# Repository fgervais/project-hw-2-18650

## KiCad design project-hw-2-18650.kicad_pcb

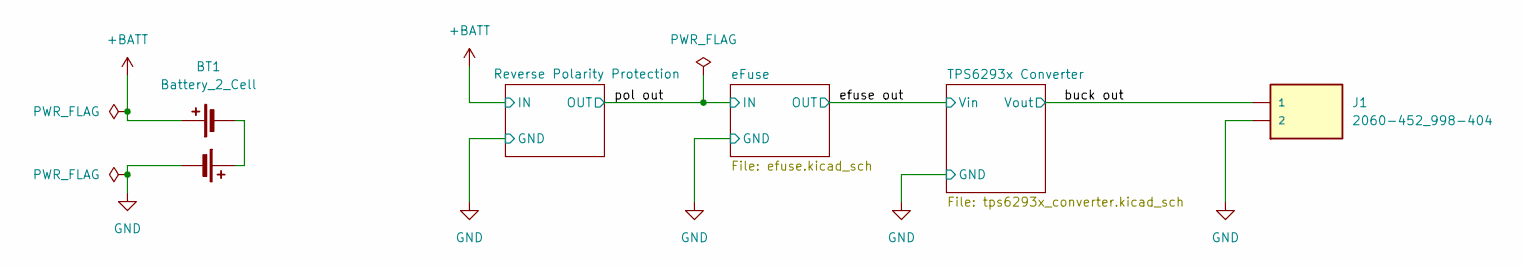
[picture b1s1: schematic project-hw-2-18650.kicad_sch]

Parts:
BT1: Battery_2_Cell; Keystone_1049P
J1: 2060-452_998-404; WAGO_2060-452_998-404; PARTREV N/A

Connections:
+BATT: BT1.1 (+); also elsewhere on the board
/buck out: J1.1_1 (1), J1.1_2 (1); also elsewhere on the board
GND: BT1.3 (-), J1.2_1 (2), J1.2_2 (2); also elsewhere on the board
unnamed: BT1.2 (-), BT1.4 (+)

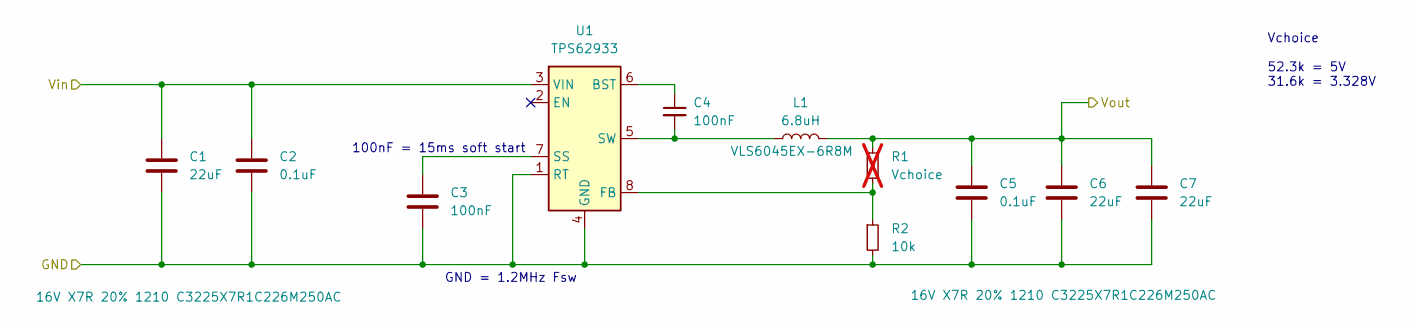
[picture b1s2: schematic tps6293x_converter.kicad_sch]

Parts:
C1, C6, C7: 22uF; C_1210_3225Metric
C2, C5: 0.1uF; C_0603_1608Metric
C3, C4: 100nF; C_0603_1608Metric
L1: 6.8uH; L_TDK_VLS6045EX_VLS6045AF
R1: Vchoice; 0603_1608Metric_DNI_NoPaste; not fitted
R2: 10k; R_0603_1608Metric
U1: TPS62933; SOT-583-8

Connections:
/buck out: C5.1, C6.1, C7.1, L1.2, R1.1; also elsewhere on the board
/efuse out: C1.1, C2.1, U1.3 (VIN); also elsewhere on the board
GND: C1.2, C2.2, C3.2, C5.2, C6.2, C7.2, R2.2, U1.1 (RT), U1.4 (GND); also elsewhere on the board
unnamed: C4.1, U1.6 (BST)
unnamed: R1.2, R2.1, U1.8 (FB)
unnamed: C3.1, U1.7 (SS)
unnamed: C4.2, L1.1, U1.5 (SW)

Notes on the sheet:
100nF = 15ms soft start
Vchoice 52.3k = 5V 31.6k = 3.328V
GND = 1.2MHz Fsw

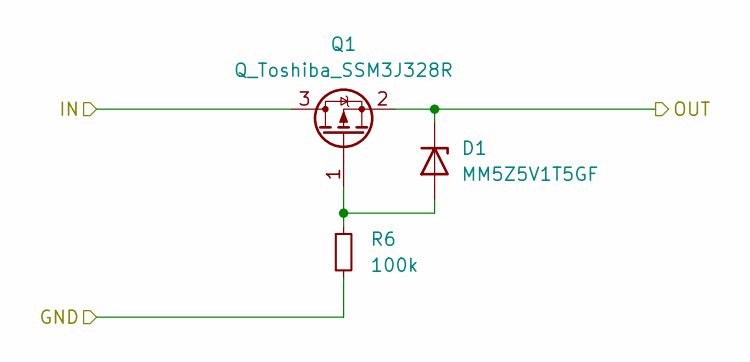
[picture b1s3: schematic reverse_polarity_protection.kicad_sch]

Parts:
D1: MM5Z5V1T5GF; D_SOD-523
Q1: Q_Toshiba_SSM3J328R; SOT-23F
R6: 100k; R_0603_1608Metric

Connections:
+BATT: Q1.3 (D); also elsewhere on the board
/pol out: D1.1 (K), Q1.2 (S); also elsewhere on the board
GND: R6.2; also elsewhere on the board
unnamed: D1.2 (A), Q1.1 (G), R6.1

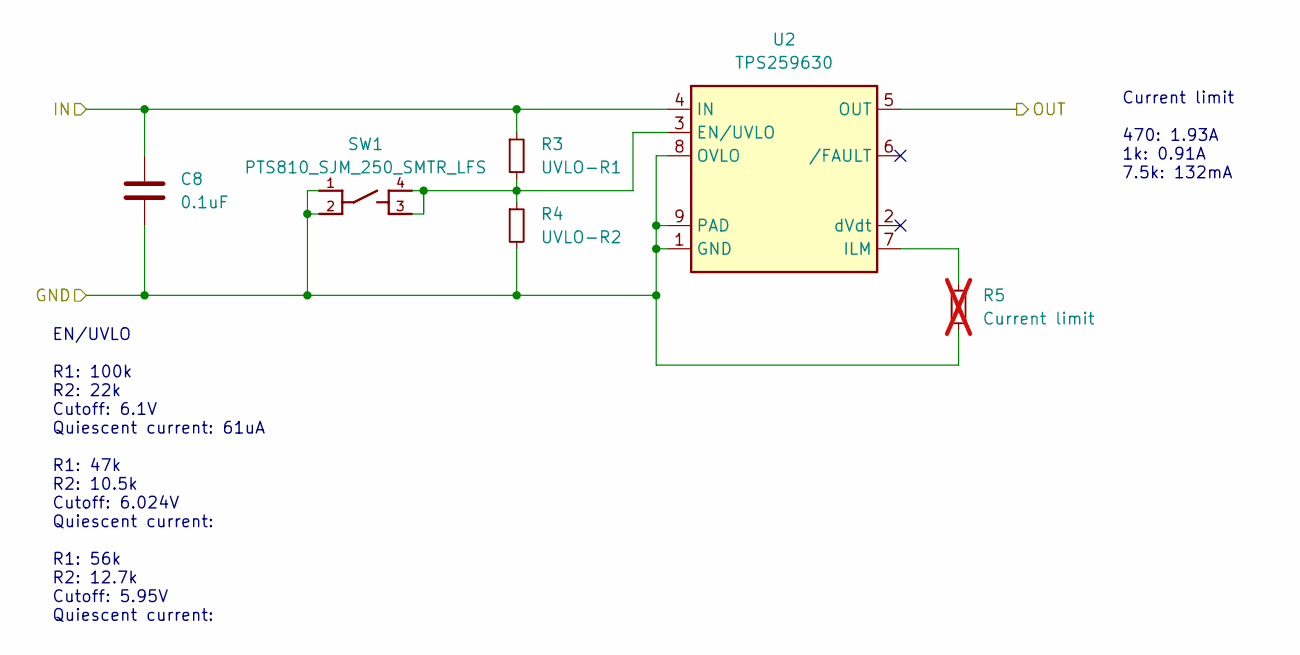
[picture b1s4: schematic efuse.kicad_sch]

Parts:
C8: 0.1uF; C_0603_1608Metric
R3: UVLO-R1; R_0603_1608Metric
R4: UVLO-R2; R_0603_1608Metric
R5: Current limit; 0603_1608Metric_DNI_NoPaste; not fitted
SW1: PTS810_SJM_250_SMTR_LFS; SW_PTS810_SJM_250_SMTR_LFS; DigiKey_Part_Number CKN10502TR-ND
U2: TPS259630; TI_SO-PowerPAD-8

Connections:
/efuse out: U2.5 (OUT); also elsewhere on the board
/pol out: C8.1, R3.1, U2.4 (IN); also elsewhere on the board
GND: C8.2, R4.2, R5.2, SW1.1, SW1.2, U2.1 (GND), U2.8 (OVLO), U2.9 (PAD); also elsewhere on the board
unnamed: R3.2, R4.1, SW1.3, SW1.4, U2.3 (EN/UVLO)
unnamed: R5.1, U2.7 (ILM)

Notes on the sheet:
Current limit 470: 1.93A 1k: 0.91A 7.5k: 132mA
EN/UVLO R1: 100k R2: 22k Cutoff: 6.1V Quiescent current: 61uA R1: 47k R2: 10.5k Cutoff: 6.024V Quiescent current: R1: 56k R2: 12.7k Cutoff: 5.95V Quiescent current:

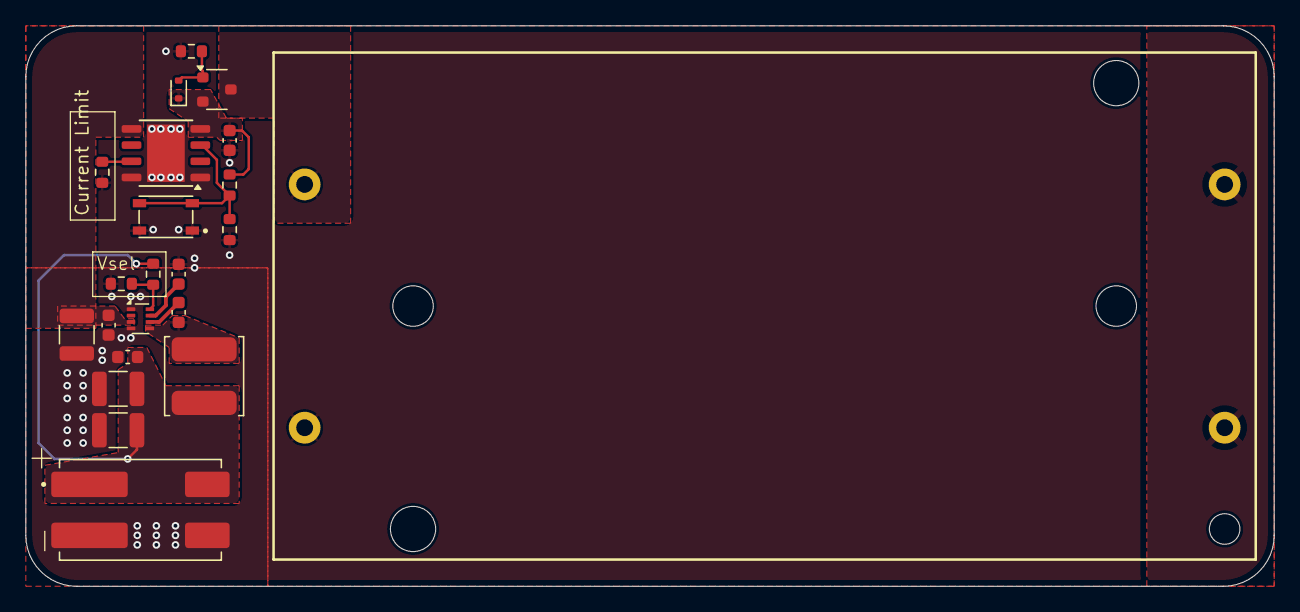
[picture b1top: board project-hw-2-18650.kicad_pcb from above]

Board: 2 copper layers, 98.0 x 44.0 mm, 22 parts (0 on the bottom side), 13 nets.

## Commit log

2025-09-26 Create blank project
2025-09-27 sch: first draft
2025-09-27 sch: assign correct footprint
2025-09-27 pcb: first draft
2025-09-27 pcb: change DNI footprint
2025-09-27 pcb: add ground backplane
2025-09-28 pcb: routing v2
2025-09-28 sch: change input cap value
2025-09-28 pcb: change cell series connection width
2025-09-28 pcb: add thermal relief on bootstrap cap
2025-09-28 pcb: add ground vias
2025-09-28 add: version
2025-09-29 sch: add efuse
2025-09-29 pcb: place efuse
2025-09-30 pcb: first complete routing
2025-10-01 pcb: change the solder bridge shape
2025-10-01 sch: fix capacitor description
2025-10-02 Update version silkscreen
2025-10-02 Add gerbers
2025-10-02 sch: change undervoltage resistor value
2025-10-04 pcb: update Keystone_1049P footprint
2025-10-04 sch: add reverse polarity protection
2025-10-04 pcb: route reverse polarity protection
2025-10-04 pcb: flip resistor
2025-10-04 pcb: make bat zone bigger
2025-10-04 pcb: update version
2025-10-04 Update gerbers
2025-10-05 Change gerbers to JLCPCB requirements
2025-10-05 Fix TI_SO-PowerPAD-8 pad soldermask
2025-10-05 Update silkscreen version
2025-10-05 Close kicad
2025-10-05 Run DRC again
2025-10-15 Add assembly file
2025-10-18 Add clarity to the choice resistors
2025-10-19 Add max input voltage information
